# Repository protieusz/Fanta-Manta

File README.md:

# Fanta-Manta

Resurrection of the Manta closed source pcb by rainkeebs using Waveshare RP2040 zero.
Generously sponsored by jcastaneda from MechWild discord.

I did the design as closely to the originaly rainkeebs design as much as possible with the difference of using a RP2040 instead of Pro Micro.
This design resurrection was blessed by rainkeebs himself.
PCBs are currently in production. 1 Aug 2023.

Print the designs at your own risk.  No support is given. Thanks.

I accept any tips or donations of a cup of coffee to help keep me motivate but you don't have to if you don't want to. Thanks. https://ko-fi.com/protieusz
Update: 18 Aug 2023

Final Product Build

Unboxing

Front

Back

Test Fitting

PCB model

Front side

Bottom side. Fanta-Manta logo by jcastaneda

This logo is from https://logowik.com/fanta-new-vector-logo-3767.html

Case

Meme Add Case 3 Aug 2023

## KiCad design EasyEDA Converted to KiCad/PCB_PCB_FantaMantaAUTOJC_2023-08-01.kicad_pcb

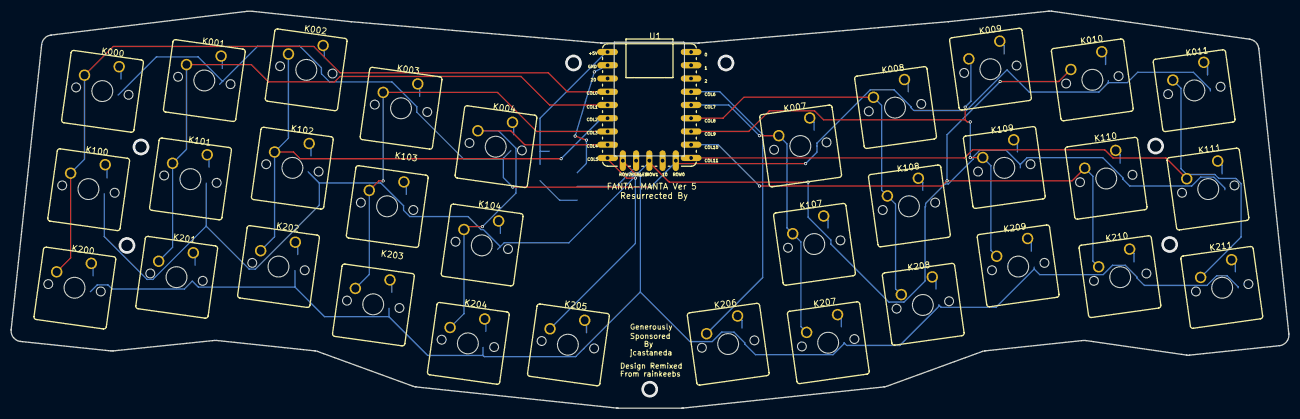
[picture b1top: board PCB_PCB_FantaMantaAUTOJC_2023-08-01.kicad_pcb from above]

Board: 2 copper layers, 245.1 x 76.1 mm, 67 parts (0 on the bottom side), 51 nets.

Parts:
1: Sacrifical pixel; LEDSTRIP-3P
D000, D001, D002, D003, D004, D007, D008, D009, D010, D011, D100, D101, D102, D103, D104, D107, D108, D109, D110, D111, D200, D201, D202, D203, D204, D205, D206, D207, D208, D209, D210, D211, D212: SM4007PL; SOD-123F_L2.8-W1.8-LS3.7-RD
K000, K001, K002, K003, K004, K007, K008, K009, K010, K011, K100, K101, K102, K103, K104, K107, K108, K109, K110, K111, K200, K201, K202, K203, K204, K205, K206, K207, K208, K209, K210, K211: 100; CHERRY_MX_100_MILLMAX
U1: RP2040-ZERO_WAVESHARE - with GPIO; RP2040-ZERO_WAVESHARE- W/ GPIO

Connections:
1_A: 1.A, D212.1
+5V: D212.2, U1.22
COL0: K000.2, K100.2, K200.2, U1.19
COL1: K001.2, K101.2, K201.2, U1.18
COL2: K002.2, K102.2, K202.2, U1.17
COL3: K003.2, K103.2, K203.2, U1.16
COL4: K004.2, K104.2, K204.2, U1.15
COL5: K205.2, U1.14
COL6: K206.2, U1.3
COL7: K007.2, K107.2, K207.2, U1.4
COL8: K008.2, K108.2, K208.2, U1.5
COL9: K009.2, K109.2, K209.2, U1.6
COL10: K010.2, K110.2, K210.2, U1.7
COL11: K011.2, K111.2, K211.2, U1.8
D111_2: D111.2, K111.1
D205_2: D205.2, K205.1
D206_2: D206.2, K206.1
GND: 1.C, U1.21
K000_1: D000.2, K000.1
K001_1: D001.2, K001.1
K002_1: D002.2, K002.1
K003_1: D003.2, K003.1
K004_1: D004.2, K004.1
K007_1: D007.2, K007.1
K008_1: D008.2, K008.1
K009_1: D009.2, K009.1
K010_1: D010.2, K010.1
K011_1: D011.2, K011.1
K100_1: D100.2, K100.1
K101_1: D101.2, K101.1
K102_1: D102.2, K102.1
K103_1: D103.2, K103.1
K104_1: D104.2, K104.1
K107_1: D107.2, K107.1
K108_1: D108.2, K108.1
K109_1: D109.2, K109.1
K110_1: D110.2, K110.1
K200_1: D200.2, K200.1
K201_1: D201.2, K201.1
K202_1: D202.2, K202.1
K203_1: D203.2, K203.1
K204_1: D204.2, K204.1
K207_1: D207.2, K207.1
K208_1: D208.2, K208.1
K209_1: D209.2, K209.1
K210_1: D210.2, K210.1
K211_1: D211.2, K211.1
RGBLED: 1.B, U1.12
ROW0: D000.1, D001.1, D002.1, D003.1, D004.1, D007.1, D008.1, D009.1, D010.1, D011.1, U1.9
ROW1: D100.1, D101.1, D102.1, D103.1, D104.1, D107.1, D108.1, D109.1, D110.1, D111.1, U1.11
ROW2: D200.1, D201.1, D202.1, D203.1, D204.1, D205.1, D206.1, D207.1, D208.1, D209.1, D210.1, D211.1, U1.13

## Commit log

2023-08-02 FantaManta logo by jcastaneda
2023-08-02 Original dxf from rainkeebs
    Not to scale.
2023-08-02 KLE layout only
2023-08-02 Correct scale of FantaManta
2023-08-02 Extra logos not used
2023-08-02 Gerber files
2023-08-02 Converted pcb to KiCad
    Not perfect
2023-08-02 Schematic
2023-08-03 QMK source code
2023-08-03 Update keymap.c
    Add a ; at the end
2023-08-03 RP2040 firmware
2023-08-03 Update README.md
    Add meme case add on
2023-08-03 Update README.md
    Add case model
2023-08-18 Update keymap.c
    Add new combos and vol stuff
2023-08-18 Added pics
2023-08-18 Corrected the back pic
2023-08-18 remove sensitive info
2024-04-09 STL Case Files
